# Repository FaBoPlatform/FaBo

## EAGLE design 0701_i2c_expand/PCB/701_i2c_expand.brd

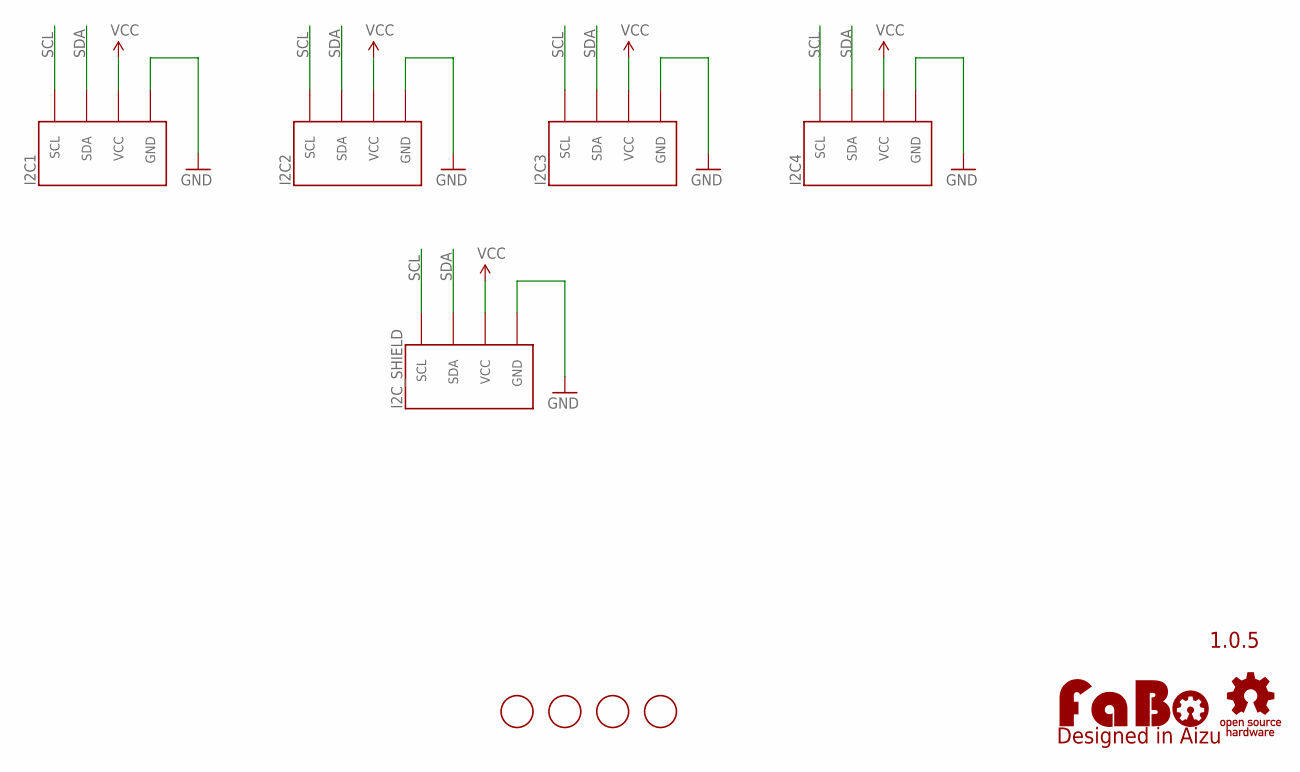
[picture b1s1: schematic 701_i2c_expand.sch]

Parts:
I2C1, I2C2, I2C3, I2C4, I2C_SHIELD: FABO_BRICK_I2C-S04B-PASK-2_LONG; FABO_BRICK_I2C_S04B-PASK-2_LONG
LOGO1: LOGO_FABO-M; LOGO_FABO_M
U$7, U$8, U$9, U$10: SCREW-PAD-3MM; SCREWPAD_3MM
U$11: LOGO_OSHW-M_BOTTOM; LOGO_OSHW_M_BOTTOM

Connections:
GND: I2C1.GND, I2C2.GND, I2C3.GND, I2C4.GND, I2C_SHIELD.GND
SCL: I2C1.SCL, I2C2.SCL, I2C3.SCL, I2C4.SCL, I2C_SHIELD.SCL
SDA: I2C1.SDA, I2C2.SDA, I2C3.SDA, I2C4.SDA, I2C_SHIELD.SDA
VCC: I2C1.VCC, I2C2.VCC, I2C3.VCC, I2C4.VCC, I2C_SHIELD.VCC

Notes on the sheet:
1.0.5

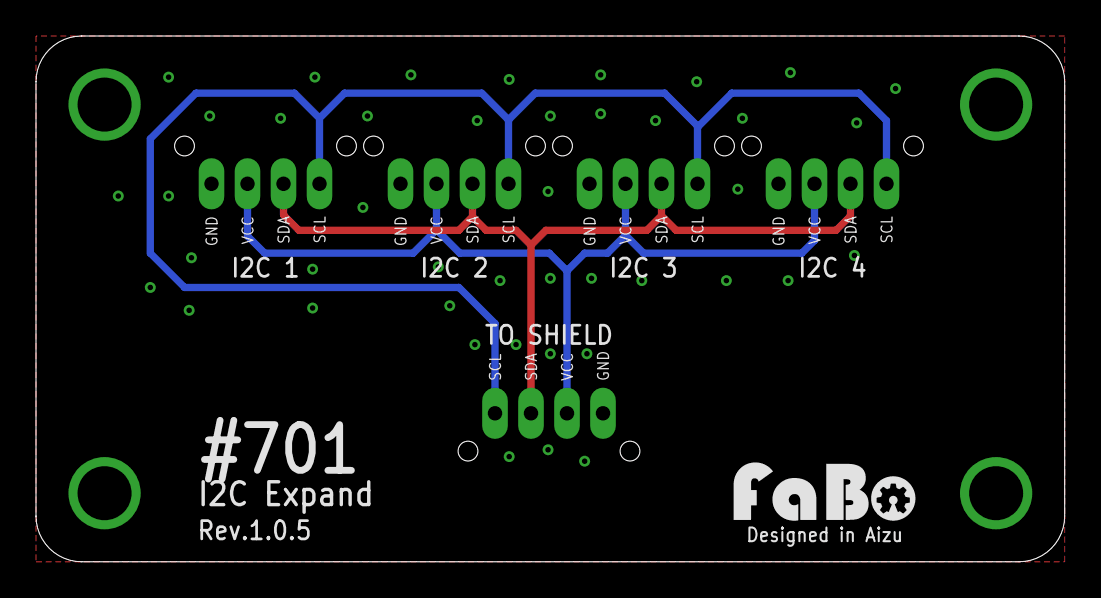
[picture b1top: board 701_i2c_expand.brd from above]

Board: 2 copper layers, 57.1 x 29.2 mm, 11 parts (0 on the bottom side), 4 nets.

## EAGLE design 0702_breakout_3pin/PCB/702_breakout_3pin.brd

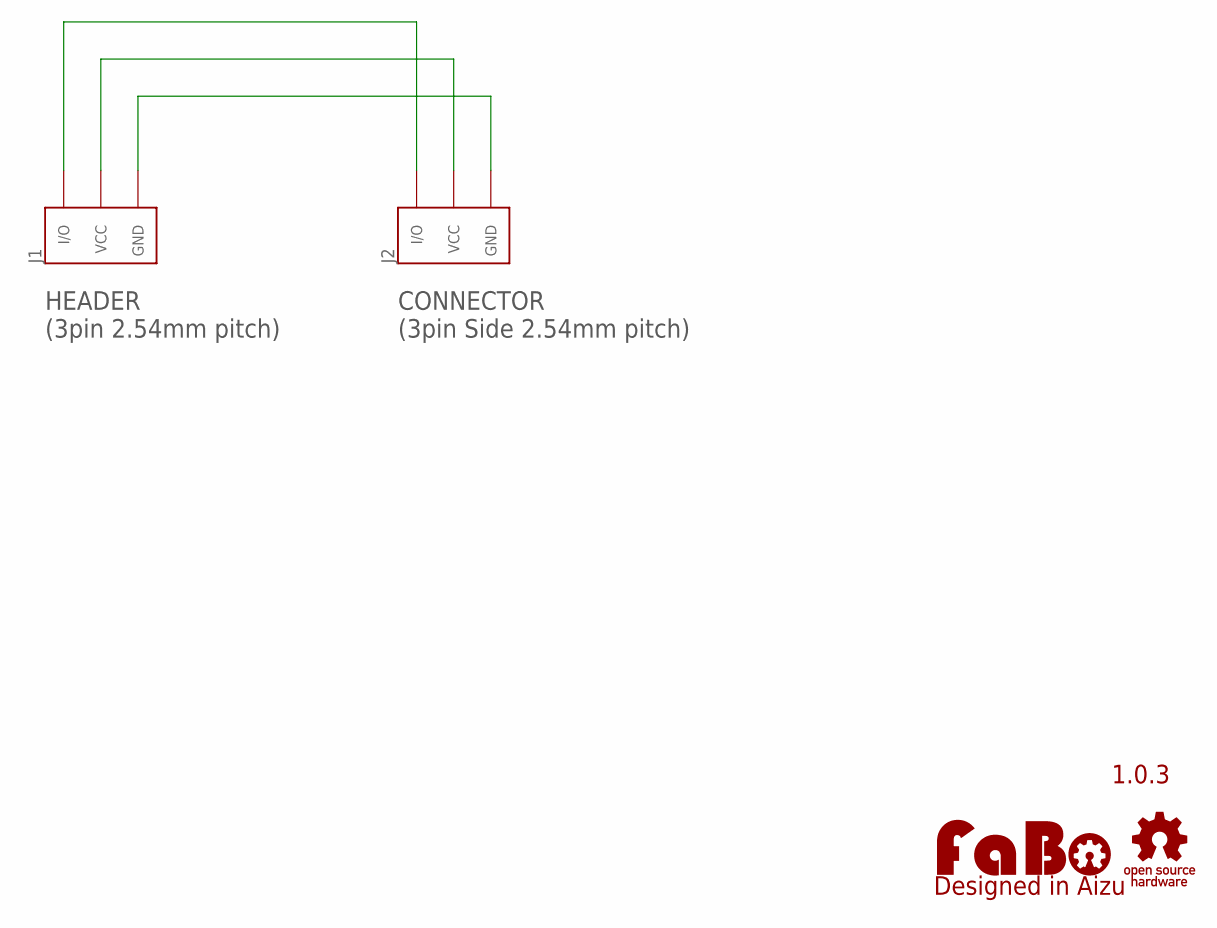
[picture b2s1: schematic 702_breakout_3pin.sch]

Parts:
J1: FABO_BRICK_3PIN-BREAKOUT; FABO_BRICK_3PIN_BREAKOUT
J2: FABO_BRICK_3PIN-CONNECTOR; FABO_BRICK_3PIN_CONNECTOR
U$2: LOGO_FABO-M_BOTTOM; LOGO_FABO_MS_BOTTOM
U$3: LOGO_OSHW-S_BOTTOM; LOGO_OSHW_S_BOTTOM

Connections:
GND: J1.GND, J2.GND
IO: J1.I/O, J2.IN/OUT (I/O)
VCC: J1.VCC, J2.VCC

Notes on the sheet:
1.0.3
CONNECTOR (3pin Side 2.54mm pitch)
HEADER (3pin 2.54mm pitch)

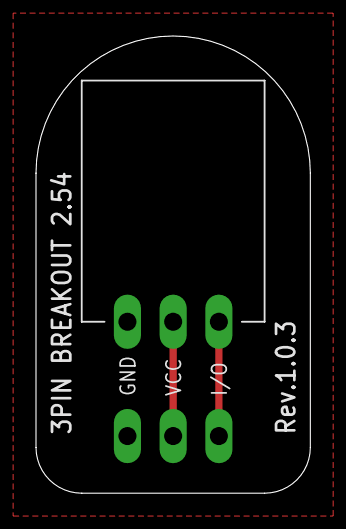
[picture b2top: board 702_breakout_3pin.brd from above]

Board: 2 copper layers, 15.2 x 25.4 mm, 4 parts (0 on the bottom side), 3 nets.

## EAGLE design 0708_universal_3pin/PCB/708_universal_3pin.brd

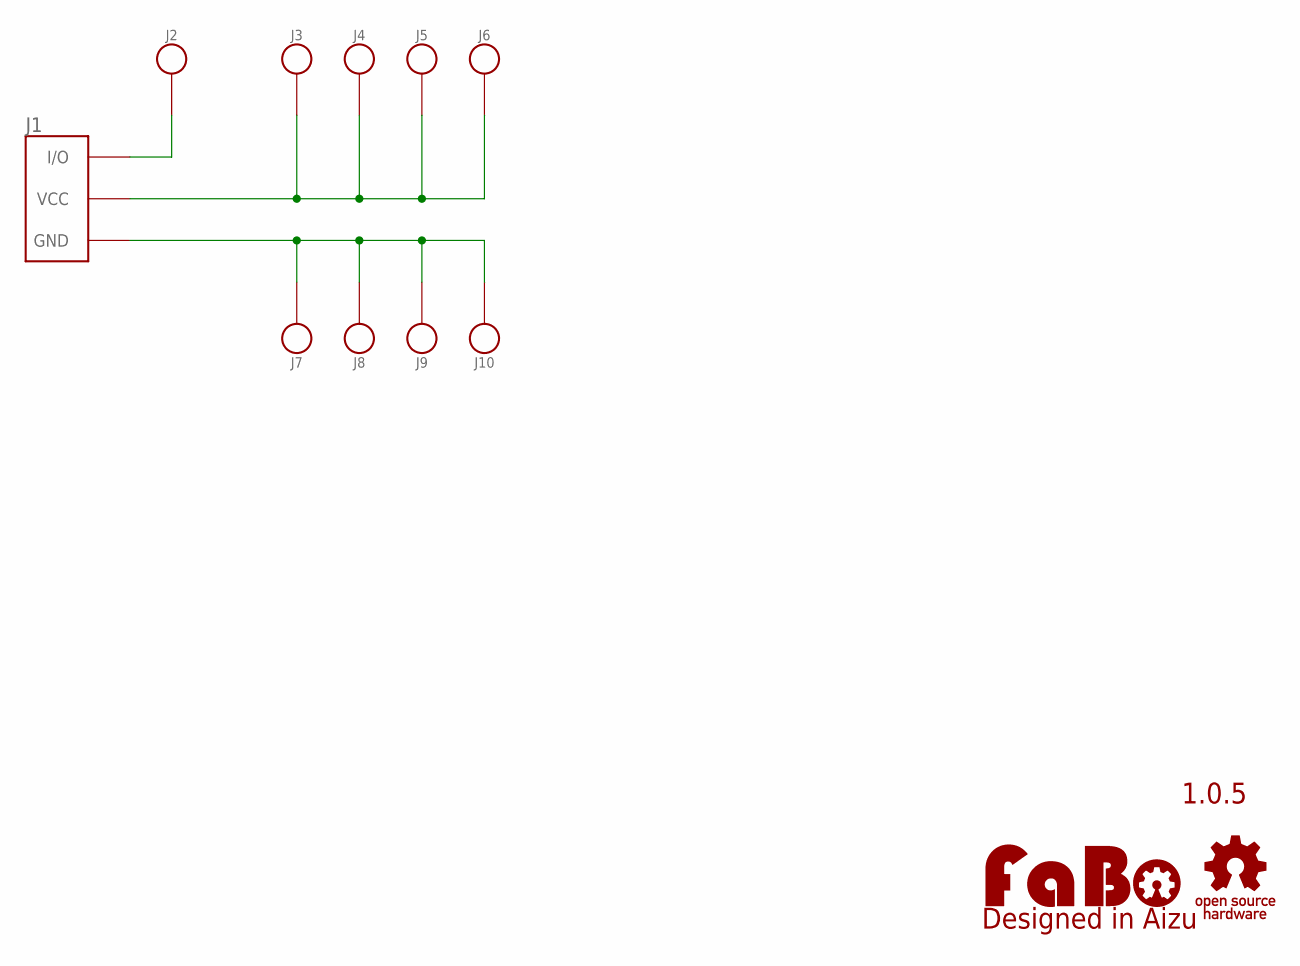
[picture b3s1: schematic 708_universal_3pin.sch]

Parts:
J1: FABO_BRICK_3PIN-UNIVERSAL; FABO_BRICK_3PIN_UNIVERSAL
J2, J3, J4, J5, J6, J7, J8, J9, J10: PIN_HEADER_1X1_NOLABEL; PIN_1X1_NOLABEL
U$1: LOGO_OSHW-M_BOTTOM; LOGO_OSHW_M_BOTTOM
U$3: LOGO_FABO-M_BOTTOM; LOGO_FABO_MS_BOTTOM

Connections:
GND: J1.GND, J7.1, J8.1, J9.1, J10.1
IO: J1.I/O, J2.1
VCC: J1.VCC, J3.1, J4.1, J5.1, J6.1

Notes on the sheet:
1.0.5

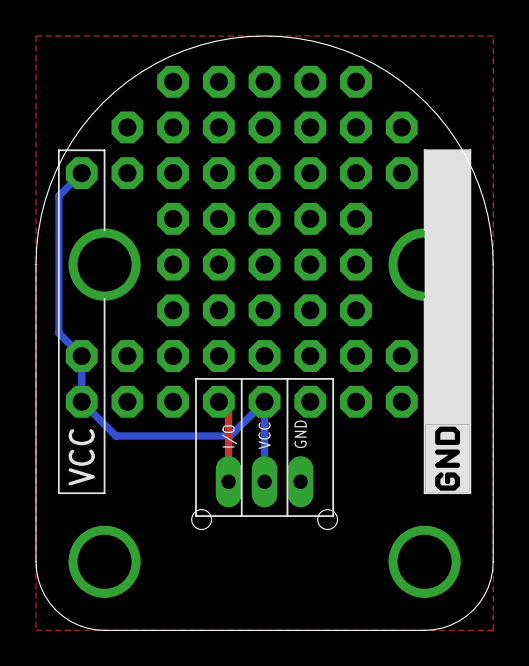
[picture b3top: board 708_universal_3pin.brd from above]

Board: 2 copper layers, 25.4 x 33.0 mm, 13 parts (0 on the bottom side), 3 nets.

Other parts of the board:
U$4: LOGO_SILK_GND

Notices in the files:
parts and their libraries:
FaBo-etc: Released under the Creative Commons Attribution-ShareAlike 4.0 License
https://creativecommons.org/licenses/by-sa/4.0
FaBo-etc: Released under the Creative Commons
